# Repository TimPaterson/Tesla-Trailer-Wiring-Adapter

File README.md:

# Tesla Model S Trailer Wiring Adapter
A typical way to add trailer wiring to any vehicle is to tap the
rear turn signal wires and one taillight wire as input to a trailer wiring module.
Unfortunately, on a Tesla Model S the taillights flash with the turn
signals if the taillights are otherswise off. So if you tap, say, the
left taillight, then all the parking lights flash on the trailer
when the left turn signal is used.

Ideally, this problem could be solved by tapping the license plate
light wire. However, that wire is in the passenger-side C-pillar and is difficult
to access compared to the taillights. This device solves the problem
by using a tap on *both* taillights, requiring both to be on for the
wiring module to enable the trailer parking lights.

**IMPORTANT!** This device is not designed the drive the trailer lights
directly. It must be connected to a trailer wiring module.

### Building It
Total parts cost for the device is around $5, not including shipping.
Here is the parts list:

|Qty|Component          |Source    |Part No.|
|---|---------          |------    |--------|
| 1 |DMC3025LSD, SOIC   |Digi-Key  |DMC3025LSD-13DICT-ND|
| 2 |47k resistor, 0603 |Digi-Key  |A129708CT-ND|
| 4 |#6 ring terminal   |Digi-Key  |A1060-ND|
|   |alternate for above|Home Depot|283218|
| 4 |#6-32 x 1/4" screw |Home Depot|766276|
| 4 |#6-32 lock nut     |Home Depot|321541|
| 1 |PCB                |OSH Park  |[https://oshpark.com/shared_projects/NLgesyix](https://oshpark.com/shared_projects/NLgesyix)|

Assembling this project requires soldering surface-mount devices (SMDs),
but they are as big as SMDs get and should be doable even for a first-timer.
Before assembling, file the nubs off the sides of the PCB so it will fit
in the enclosure.

An enclosure design is included in STL format for 3D printing. It's Fusion 360 design
file is also included.

### Connecting It
The two terminals on the left side, labeled "IN", connect to taps on the left
and right taillight wires. The terminal labeled "OUT" connects to the trailer
wiring module parking light input. The terminal labeled "GND" must be connected to the chassis,
probably at the same point as the trailer wiring module.

### Buying an Assembled Unit
If it's worth $30 to you to buy one assembled, express your interest in a discussion.

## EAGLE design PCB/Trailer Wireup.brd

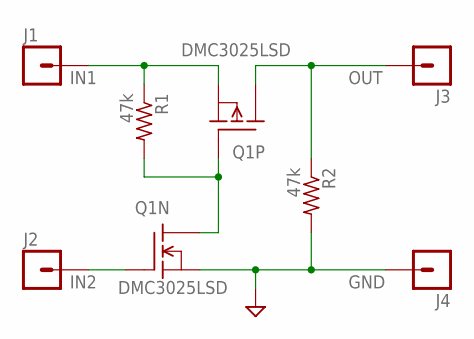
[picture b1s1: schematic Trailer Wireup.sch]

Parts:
J1, J2, J3, J4: CONN-1-SCREW-#6-0.3IN; SCREW_TERMINAL-#6-0.3IN
Q1: DMC3025LSD; SO8
R1, R2: 47k; 0603

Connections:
GND: J4.1, Q1.1 (S), R2.2
IN1: J1.1, Q1.3 (S), R1.1
IN2: J2.1, Q1.2 (G)
unnamed: Q1.4 (G), Q1.7 (D), Q1.8 (D), R1.2
OUT: J3.1, Q1.5 (D), Q1.6 (D), R2.1

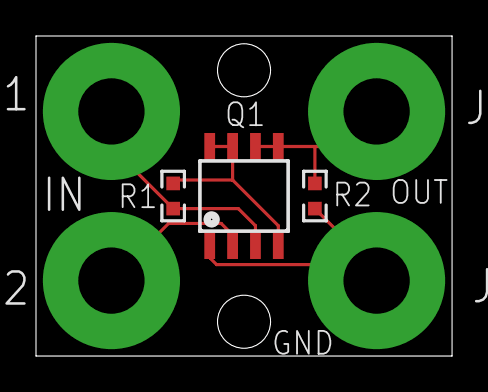
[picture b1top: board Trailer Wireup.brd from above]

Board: 2 copper layers, 23.1 x 17.8 mm, 7 parts (0 on the bottom side), 5 nets.

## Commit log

2023-04-20 fix images
